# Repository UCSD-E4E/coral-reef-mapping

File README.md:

# coral-reef-mapping
Underwater depth/heading sensor for use by SIO oceanographers in mapping coral reefs.

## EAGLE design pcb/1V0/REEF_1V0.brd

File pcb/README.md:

# PCB Work

### Note - In general, all PCB designs that get fabbed should be uploaded here. 

**8-24-18 -** 
The current PCB design (1.1) is close to functional. It is very similar to 1.0, but with different 7-segment displays, plus a couple different parts. It is 127 mm x 127 mm. This is problematic in that board prices go way down when the dimensions hit 100 mm x 100 mm. It is also problematic in that the magneometer's pads are super close together, so minimum trace spacing has to be 5 mm, which makes the board more expensive. Also, cost aside, soldering this magnetomer is a pain and hard to do right. 

The next step in the PCB domain is to create a new PCB (let's call it 2.0) that will be smaller and will have a different magnetometer. It will also have battery discharge protection circuitry, and probably some other changes. In order to make the small size feasible, we'll probably have to transistion to physically smaller parts. I think SMD parts are the answer here - we can find SMD resistors, capacitors, LEDs, LED drivers, and microcontroller. It seems to me like a lot of these parts come in a variety of sizes (for example, maybe there's 10+ standard sizes of SMD capacitors), so we probably just want to find whatever is the smallest size we think we can easily solder. Some of this info is reiterated in the hardware section if you want to read more.

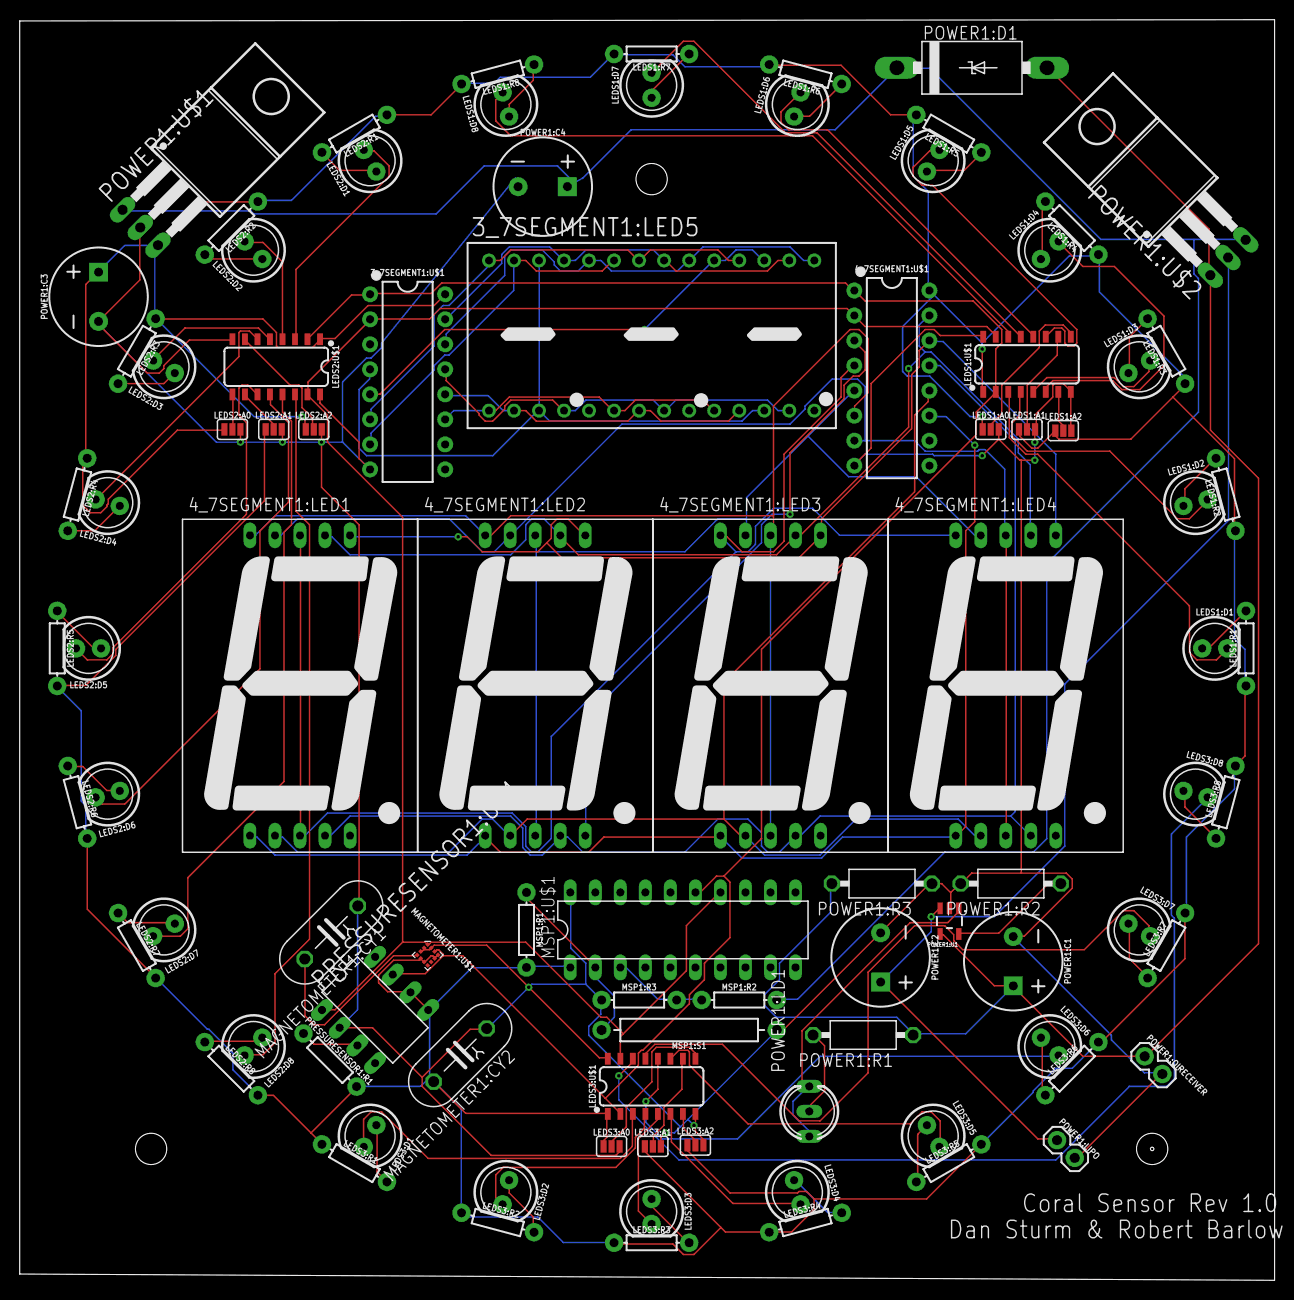
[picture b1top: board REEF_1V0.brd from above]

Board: 2 copper layers, 127.4 x 127.9 mm, 91 parts (0 on the bottom side), 90 nets.

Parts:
3_7SEGMENT1:LED5: BA56-11EWA; BA/BC56
3_7SEGMENT1:U$1, 4_7SEGMENT1:U$1: MAX6958BAPE+; DIP16
4_7SEGMENT1:LED1, 4_7SEGMENT1:LED2, 4_7SEGMENT1:LED3, 4_7SEGMENT1:LED4: 7-SEG_SA10-21; SA10-21
LEDS1:A0, LEDS1:A1, LEDS1:A2, LEDS2:A0, LEDS2:A1, LEDS2:A2, LEDS3:A0, LEDS3:A1, LEDS3:A2: SMT-JUMPER_3_NO_SILK
LEDS1:D1, LEDS1:D2, LEDS1:D3, LEDS1:D4, LEDS1:D5, LEDS1:D6, LEDS1:D7, LEDS1:D8, LEDS2:D1, LEDS2:D2, LEDS2:D3, LEDS2:D4, LEDS2:D5, LEDS2:D6, LEDS2:D7, LEDS2:D8, LEDS3:D1, LEDS3:D2, LEDS3:D3, LEDS3:D4, LEDS3:D5, LEDS3:D6, LEDS3:D7, LEDS3:D8: LED_5MM
LEDS1:R1, LEDS1:R2, LEDS1:R3, LEDS1:R4, LEDS1:R5, LEDS1:R6, LEDS1:R7, LEDS1:R8, LEDS2:R1, LEDS2:R2, LEDS2:R3, LEDS2:R4, LEDS2:R5, LEDS2:R6, LEDS2:R7, LEDS2:R8, LEDS3:R1, LEDS3:R2, LEDS3:R3, LEDS3:R4, LEDS3:R5, LEDS3:R6, LEDS3:R7, LEDS3:R8: 100; AXIAL-0.3
LEDS1:U$1, LEDS2:U$1, LEDS3:U$1: TPIC2810D; SO16
MAGNETOMETER1:CY1, MAGNETOMETER1:CY2: 100nF; YC7B5
MAGNETOMETER1:U$1: LGA-12
MSP1:R1: 100K; AXIAL-0.3
MSP1:R2, MSP1:R3: 100k; AXIAL-0.3
MSP1:S1: REED_SWITCH-PTH-GLASS; REED_SWITCH_GLASS
MSP1:U$1: MSP430G2452IN20; DIL20
POWER1:C1, POWER1:C2: 4.7uF; CPOL-RADIAL-5MM-10MM
POWER1:C3, POWER1:C4: 1uF; CPOL-RADIAL-5MM-10MM
POWER1:D1: 1N5908; C4111-15
POWER1:LD1: DUOLED-A-5MM
POWER1:LIPO, POWER1:QIRECEIVER: 1X02
POWER1:R1: 470; VMTA55
POWER1:R2: 2K; VMTA55
POWER1:R3: 100K; VMTA55
POWER1:U1: MCP73831; SOT23-5
POWER1:U$1: MCP1826S; T03B
POWER1:U$2: IPP80P03P4L-04; T03B
PRESSURESENSOR1:R1: 10k; AXIAL-0.3
PRESSURESENSOR1:U$1: MS5803-14BA; DIL8

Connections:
3.3V: 3_7SEGMENT1:U$1.16, 4_7SEGMENT1:U$1.16, LEDS1:A0.1, LEDS1:A1.1, LEDS1:A2.1, LEDS1:R1.P$1, LEDS1:R2.P$1, LEDS1:R3.P$1, LEDS1:R4.P$1, LEDS1:R5.P$2, LEDS1:R6.P$2, LEDS1:R7.P$2, LEDS1:R8.P$2, LEDS1:U$1.1, LEDS2:A0.1, LEDS2:A1.1, LEDS2:A2.1, LEDS2:R1.P$1, LEDS2:R2.P$1, LEDS2:R3.P$1, LEDS2:R4.P$1, LEDS2:R5.P$2, LEDS2:R6.P$2, LEDS2:R7.P$2, LEDS2:R8.P$2, LEDS2:U$1.1, LEDS3:A0.1, LEDS3:A1.1, LEDS3:A2.1, LEDS3:R1.P$1, LEDS3:R2.P$1, LEDS3:R3.P$1, LEDS3:R4.P$1, LEDS3:R5.P$2, LEDS3:R6.P$2, LEDS3:R7.P$2, LEDS3:R8.P$2, LEDS3:U$1.1, MAGNETOMETER1:CY2.2, MAGNETOMETER1:U$1.5, MAGNETOMETER1:U$1.6, MAGNETOMETER1:U$1.9, MAGNETOMETER1:U$1.10, MSP1:R1.P$2, MSP1:U$1.1, POWER1:C3.+, POWER1:U$1.3, PRESSURESENSOR1:R1.P$2, PRESSURESENSOR1:U$1.5, PRESSURESENSOR1:U$1.6
3_7SEGMENT1:N$1: 3_7SEGMENT1:LED5.3, 3_7SEGMENT1:LED5.12, 3_7SEGMENT1:LED5.26, 3_7SEGMENT1:U$1.4
3_7SEGMENT1:N$8: 3_7SEGMENT1:LED5.16, 3_7SEGMENT1:LED5.21, 3_7SEGMENT1:LED5.25, 3_7SEGMENT1:U$1.15
3_7SEGMENT1:N$9: 3_7SEGMENT1:LED5.15, 3_7SEGMENT1:LED5.20, 3_7SEGMENT1:LED5.24, 3_7SEGMENT1:U$1.14
3_7SEGMENT1:N$10: 3_7SEGMENT1:LED5.4, 3_7SEGMENT1:LED5.8, 3_7SEGMENT1:LED5.13, 3_7SEGMENT1:U$1.13
3_7SEGMENT1:N$11: 3_7SEGMENT1:LED5.2, 3_7SEGMENT1:LED5.7, 3_7SEGMENT1:LED5.11, 3_7SEGMENT1:U$1.12
3_7SEGMENT1:N$26: 3_7SEGMENT1:LED5.1, 3_7SEGMENT1:LED5.6, 3_7SEGMENT1:LED5.10, 3_7SEGMENT1:U$1.11
3_7SEGMENT1:N$28: 3_7SEGMENT1:LED5.17, 3_7SEGMENT1:LED5.19, 3_7SEGMENT1:U$1.5
3_7SEGMENT1:N$29: 3_7SEGMENT1:LED5.23, 3_7SEGMENT1:LED5.27, 3_7SEGMENT1:U$1.7
3_7SEGMENT1:N$30: 3_7SEGMENT1:LED5.18, 3_7SEGMENT1:LED5.22, 3_7SEGMENT1:LED5.28, 3_7SEGMENT1:U$1.6
4_7SEGMENT1:N$1: 4_7SEGMENT1:LED1.7, 4_7SEGMENT1:LED2.7, 4_7SEGMENT1:LED3.7, 4_7SEGMENT1:LED4.7, 4_7SEGMENT1:U$1.15
4_7SEGMENT1:N$2: 4_7SEGMENT1:LED1.6, 4_7SEGMENT1:LED2.6, 4_7SEGMENT1:LED3.6, 4_7SEGMENT1:LED4.6, 4_7SEGMENT1:U$1.14
4_7SEGMENT1:N$3: 4_7SEGMENT1:LED1.4, 4_7SEGMENT1:LED2.4, 4_7SEGMENT1:LED3.4, 4_7SEGMENT1:LED4.4, 4_7SEGMENT1:U$1.13
4_7SEGMENT1:N$4: 4_7SEGMENT1:LED1.2, 4_7SEGMENT1:LED2.2, 4_7SEGMENT1:LED3.2, 4_7SEGMENT1:LED4.2, 4_7SEGMENT1:U$1.12
4_7SEGMENT1:N$5: 4_7SEGMENT1:LED1.1, 4_7SEGMENT1:LED2.1, 4_7SEGMENT1:LED3.1, 4_7SEGMENT1:LED4.1, 4_7SEGMENT1:U$1.11
4_7SEGMENT1:N$6: 4_7SEGMENT1:LED1.3, 4_7SEGMENT1:LED1.8, 4_7SEGMENT1:LED3.10, 4_7SEGMENT1:LED4.10, 4_7SEGMENT1:U$1.4
4_7SEGMENT1:N$7: 4_7SEGMENT1:LED2.3, 4_7SEGMENT1:LED2.8, 4_7SEGMENT1:LED3.9, 4_7SEGMENT1:LED4.9, 4_7SEGMENT1:U$1.5
4_7SEGMENT1:N$8: 4_7SEGMENT1:LED2.5, 4_7SEGMENT1:U$1.3
4_7SEGMENT1:N$9: 4_7SEGMENT1:LED1.9, 4_7SEGMENT1:LED2.9, 4_7SEGMENT1:LED4.3, 4_7SEGMENT1:LED4.8, 4_7SEGMENT1:U$1.7
4_7SEGMENT1:N$11: 4_7SEGMENT1:LED1.10, 4_7SEGMENT1:LED2.10, 4_7SEGMENT1:LED3.3, 4_7SEGMENT1:LED3.8, 4_7SEGMENT1:U$1.6
GND: 3_7SEGMENT1:U$1.8, 4_7SEGMENT1:U$1.8, LEDS1:A0.3, LEDS1:A1.3, LEDS1:A2.3, LEDS1:U$1.8, LEDS1:U$1.16, LEDS2:A0.3, LEDS2:A1.3, LEDS2:A2.3, LEDS2:U$1.8, LEDS2:U$1.16, LEDS3:A0.3, LEDS3:A1.3, LEDS3:A2.3, LEDS3:U$1.8, LEDS3:U$1.16, MAGNETOMETER1:CY1.1, MAGNETOMETER1:CY2.1, MAGNETOMETER1:U$1.2, MAGNETOMETER1:U$1.3, MAGNETOMETER1:U$1.12, MSP1:R3.P$1, MSP1:S1.P$1, MSP1:U$1.20, POWER1:C1.-, POWER1:C2.-, POWER1:C3.-, POWER1:C4.-, POWER1:LIPO.2, POWER1:QIRECEIVER.2, POWER1:R2.2, POWER1:R3.1, POWER1:U1.2, POWER1:U$1.2, PRESSURESENSOR1:U$1.2
LEDS1:N$1: LEDS1:D1.K, LEDS1:U$1.3
LEDS1:N$2: LEDS1:D2.K, LEDS1:U$1.4
LEDS1:N$3: LEDS1:D3.K, LEDS1:U$1.5
LEDS1:N$4: LEDS1:D4.K, LEDS1:U$1.6
LEDS1:N$5: LEDS1:D5.K, LEDS1:U$1.11
LEDS1:N$6: LEDS1:D6.K, LEDS1:U$1.12
LEDS1:N$7: LEDS1:D7.K, LEDS1:U$1.13
LEDS1:N$8: LEDS1:D8.K, LEDS1:U$1.14
LEDS1:N$9: LEDS1:A2.2, LEDS1:U$1.7
LEDS1:N$10: LEDS1:A1.2, LEDS1:U$1.10
LEDS1:N$11: LEDS1:A0.2, LEDS1:U$1.9
LEDS1:N$12: LEDS1:D5.A, LEDS1:R5.P$1
LEDS1:N$13: LEDS1:D6.A, LEDS1:R6.P$1
LEDS1:N$14: LEDS1:D7.A, LEDS1:R7.P$1
LEDS1:N$15: LEDS1:D8.A, LEDS1:R8.P$1
LEDS1:N$16: LEDS1:D1.A, LEDS1:R1.P$2
LEDS1:N$18: LEDS1:D2.A, LEDS1:R2.P$2
LEDS1:N$19: LEDS1:D3.A, LEDS1:R3.P$2
LEDS1:N$20: LEDS1:D4.A, LEDS1:R4.P$2
LEDS2:N$1: LEDS2:D1.K, LEDS2:U$1.3
LEDS2:N$2: LEDS2:D2.K, LEDS2:U$1.4
LEDS2:N$3: LEDS2:D3.K, LEDS2:U$1.5
LEDS2:N$4: LEDS2:D4.K, LEDS2:U$1.6
LEDS2:N$5: LEDS2:D5.K, LEDS2:U$1.11
LEDS2:N$6: LEDS2:D6.K, LEDS2:U$1.12
LEDS2:N$7: LEDS2:D7.K, LEDS2:U$1.13
LEDS2:N$8: LEDS2:D8.K, LEDS2:U$1.14
LEDS2:N$9: LEDS2:A2.2, LEDS2:U$1.7
LEDS2:N$10: LEDS2:A1.2, LEDS2:U$1.10
LEDS2:N$11: LEDS2:A0.2, LEDS2:U$1.9
LEDS2:N$12: LEDS2:D5.A, LEDS2:R5.P$1
LEDS2:N$13: LEDS2:D6.A, LEDS2:R6.P$1
LEDS2:N$14: LEDS2:D7.A, LEDS2:R7.P$1
LEDS2:N$15: LEDS2:D8.A, LEDS2:R8.P$1
LEDS2:N$16: LEDS2:D1.A, LEDS2:R1.P$2
LEDS2:N$18: LEDS2:D2.A, LEDS2:R2.P$2
LEDS2:N$19: LEDS2:D3.A, LEDS2:R3.P$2
LEDS2:N$20: LEDS2:D4.A, LEDS2:R4.P$2
LEDS3:N$1: LEDS3:D1.K, LEDS3:U$1.3
LEDS3:N$2: LEDS3:D2.K, LEDS3:U$1.4
LEDS3:N$3: LEDS3:D3.K, LEDS3:U$1.5
LEDS3:N$4: LEDS3:D4.K, LEDS3:U$1.6
LEDS3:N$5: LEDS3:D5.K, LEDS3:U$1.11
LEDS3:N$6: LEDS3:D6.K, LEDS3:U$1.12
LEDS3:N$7: LEDS3:D7.K, LEDS3:U$1.13
LEDS3:N$8: LEDS3:D8.K, LEDS3:U$1.14
LEDS3:N$9: LEDS3:A2.2, LEDS3:U$1.7
LEDS3:N$10: LEDS3:A1.2, LEDS3:U$1.10
LEDS3:N$11: LEDS3:A0.2, LEDS3:U$1.9
LEDS3:N$12: LEDS3:D5.A, LEDS3:R5.P$1
LEDS3:N$13: LEDS3:D6.A, LEDS3:R6.P$1
LEDS3:N$14: LEDS3:D7.A, LEDS3:R7.P$1
LEDS3:N$15: LEDS3:D8.A, LEDS3:R8.P$1
LEDS3:N$16: LEDS3:D1.A, LEDS3:R1.P$2
LEDS3:N$18: LEDS3:D2.A, LEDS3:R2.P$2
LEDS3:N$19: LEDS3:D3.A, LEDS3:R3.P$2
LEDS3:N$20: LEDS3:D4.A, LEDS3:R4.P$2
MAGNETOMETER1:N$3: MAGNETOMETER1:CY1.2, MAGNETOMETER1:U$1.4
MSP1:N$1: MSP1:R1.P$1, MSP1:S1.P$2, MSP1:U$1.2
MSP1:N$2: MSP1:R2.P$1, MSP1:R3.P$2, MSP1:U$1.3
unnamed: MSP1:R2.P$2, POWER1:C4.+, POWER1:D1.C, POWER1:U$1.1, POWER1:U$2.3
POWER1:N$2: POWER1:C2.+, POWER1:LIPO.1, POWER1:U1.3, POWER1:U$2.2
POWER1:N$3: POWER1:LD1.CR, POWER1:LD1.CX, POWER1:U1.1
POWER1:N$4: POWER1:C1.+, POWER1:D1.A, POWER1:QIRECEIVER.1, POWER1:R1.1, POWER1:R3.2, POWER1:U1.4, POWER1:U$2.1
POWER1:N$6: POWER1:R2.1, POWER1:U1.5
POWER1:N$7: POWER1:LD1.A, POWER1:R1.2
PRESSURESENSOR1:N$1: PRESSURESENSOR1:R1.P$1, PRESSURESENSOR1:U$1.3
SCL: 3_7SEGMENT1:U$1.2, 4_7SEGMENT1:U$1.2, LEDS1:U$1.15, LEDS2:U$1.15, LEDS3:U$1.15, MAGNETOMETER1:U$1.1, MSP1:U$1.14, PRESSURESENSOR1:U$1.1
SDA: 3_7SEGMENT1:U$1.1, 4_7SEGMENT1:U$1.1, LEDS1:U$1.2, LEDS2:U$1.2, LEDS3:U$1.2, MAGNETOMETER1:U$1.11, MSP1:U$1.15, PRESSURESENSOR1:U$1.7

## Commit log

2018-08-24 Rename depth_sensor.c to code/depth_sensor.c
2018-08-24 Create hi
2018-08-24 Rename pcb/Board_1.brd to pcb/1.1/Board_1.brd
2018-08-24 Rename pcb/Board_1.sch to pcb/1.1/Board_1.sch
2018-08-24 Rename Board_1.brd to Board_1v1.brd
2018-08-24 Rename Board_1.sch to Board_1v1.sch
2018-08-24 Rename documentationAUGUST24.txt to documentationAUGUST24.md
2018-09-17 Create 1V0
2018-09-17 Create 1V1
2018-09-17 added my github name
2018-10-23 photo
2018-10-23 photos
2018-10-23 removed
2018-10-23 readme
2018-10-23 not sure
2018-10-23 docs
2018-10-23 datasheets
2018-10-28 Your Message

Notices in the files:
parts and their libraries:
SparkFun-Switches: Licensing: Creative Commons ShareAlike 4.0 International - https://creativecommons.org/licenses/by-sa/4.0
